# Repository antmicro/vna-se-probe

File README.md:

# VNA SE probe

Copyright (c) 2025 [Antmicro](https://www.antmicro.com)

## Overview

This project contains open hardware design files for a Vector Network Analyzer (VNA) Single Ended (SE) probe that can be used for VNA measurements on production PCBs, without the need to solder or add dedicated connectors.

### Design features

* SMA connector
* Controlled 50 Ohm impedance
* Compatible with M4 probe holder arms
* Compatible with pogo pins and measurement needles
* Probe pitch adjustable by soldering angle

## Project structure

The main directory contains [KiCad](https://www.kicad.org/) project files, a LICENSE and a README.
The remaining files are stored in the following directories:

* `img` - contains graphics for this README

## License

This project is licened under the [Apache-2.0](LICENSE) license.

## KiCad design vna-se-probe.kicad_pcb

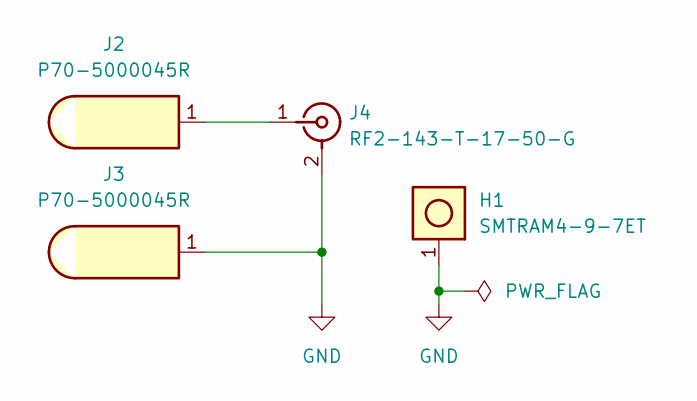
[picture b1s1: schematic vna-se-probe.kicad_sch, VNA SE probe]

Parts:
H1: MP_Terminal_M4_SMD_Horizontal_SMTRAM4-9-7ET; MPN SMTRAM4-9-7ET
J2, J3: Harwin_1x1_H2.4mm_Pad1.7mm_P70-5000045R_CUSTOM_Ed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; Harwin_1x1_H2.4mm_Pad1.7mm_P70-5000045R_CUSTOM_EdgeMount; MPN P70-5000045R
J4: Conn_SMA_RF2-143-T-17-50-G; RF_SMA_BoardEdge_RF2-143-T-17-50-G; MPN RF2-143-T-17-50-G

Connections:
GND: H1.1, J3.1, J4.2
unnamed: J2.1, J4.1

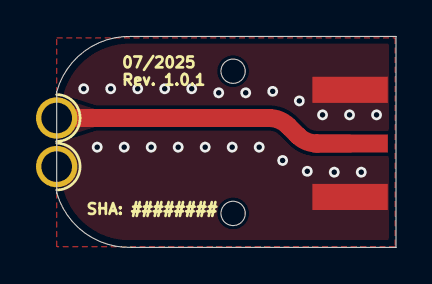
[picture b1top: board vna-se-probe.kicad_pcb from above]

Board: 4 copper layers, 18.8 x 11.7 mm, 4 parts (1 on the bottom side), 2 nets.

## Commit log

2025-07-11 [#80183] Readme: Add renders
2025-07-11 [#75263] Update annular ring and via placement
2025-07-11 [#80183] Use merged render
2025-07-11 [#80183] Update pogo pin lib link
2025-07-11 [#80183] README review
2025-07-11 [#75263] Update silkscreen, align pogopin, clean DRC
2025-07-11 [#75263] Add kicad project
2025-07-11 [#75263] Add automation
2025-07-11 [#75263] Adjust via, clean DRC and ERC
2025-07-11 [#75263] Update project
2025-07-11 [#80183] Update Readme
2025-07-11 [#75263] Initial commit
2025-07-11 [#80183] Update CI
2025-07-11 [#75263] Add test needles support
2025-07-11 [#80183] Update library links
2025-07-11 README: update, change naming for render
2025-07-11 README: Add photo
2025-07-14 [#80183] Add OHP badge

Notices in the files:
parts and their libraries:
License: Apache-2.0
